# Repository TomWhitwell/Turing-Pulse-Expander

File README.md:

# Turing-Pulse-Expander
Rev 2 Turing Pulse Expander 

This is a slightly updated version of the Turing Machine Pulse Expander, with more outputs. It uses SMD components, but is still a very easy build. 

BOM: 

- 1 x 4081 Quad AND Gate, SO14 package 
- 11 x 3mm LEDs 
- 11 x 1k resistors, 1206 package 
- 11 x 2k resistors, 1206 package (These are the LED protection resistors, if you're using high intensity LEDs they should be a different value)
- 11 x [Thonkiconn](https://www.thonk.co.uk/shop/thonkiconn-3-5mm-jack-sockets-x50/) sockets
- 1 x 16 Pin Header 2x8 (for example 649-67997-216HLF from Mouser)
- 1 x Ribbon cable

There is no panel yet in this repository.

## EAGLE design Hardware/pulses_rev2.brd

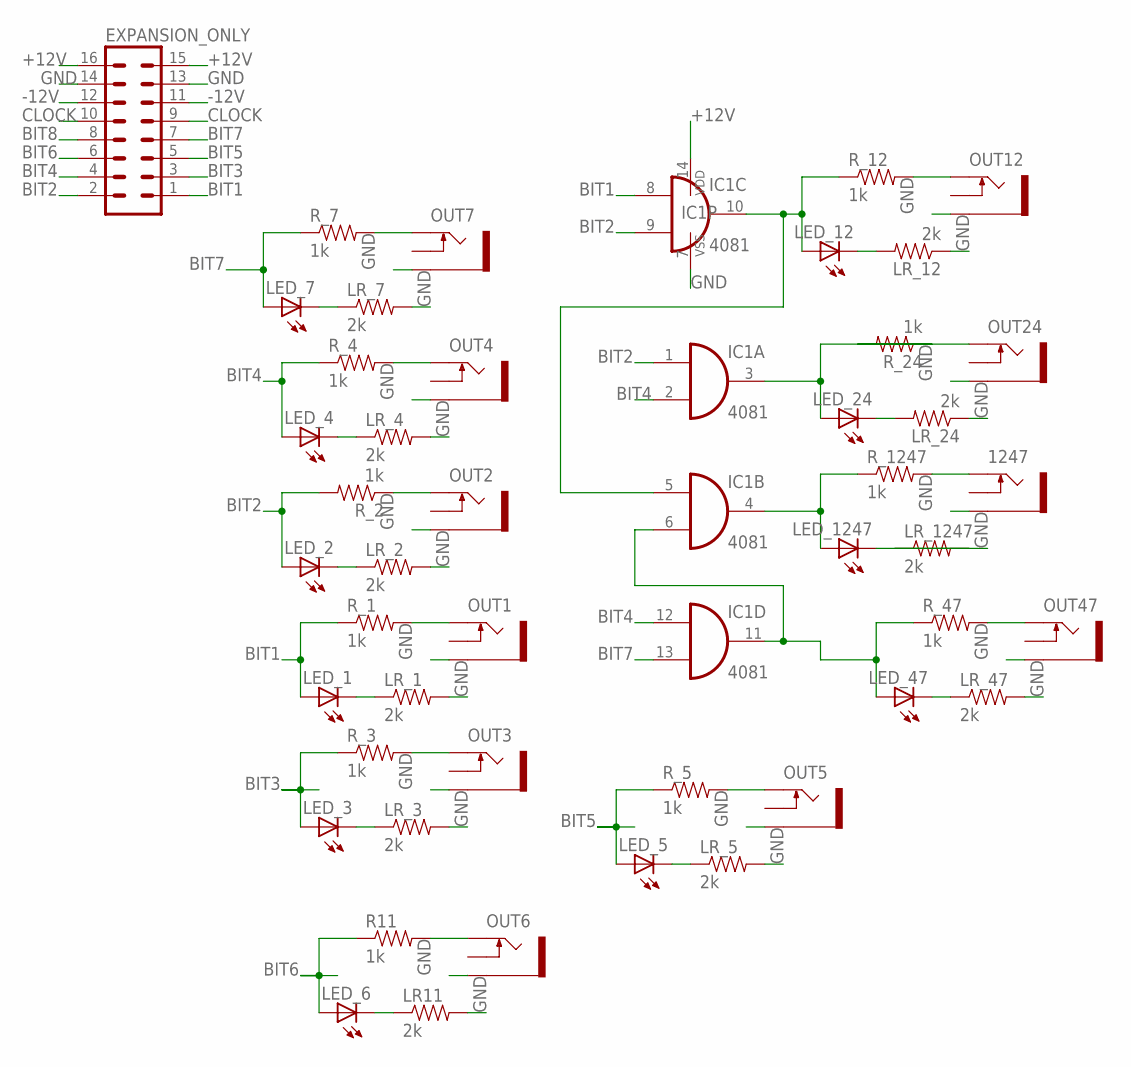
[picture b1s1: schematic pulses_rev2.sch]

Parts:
1247: THONKICONNNEW; WQP-PJ301M-12_JACK
EXPANSION_ONLY: MA08-2
IC1: 4081; SO14
LED_1, LED_2, LED_3, LED_4, LED_5, LED_6, LED_7, LED_12, LED_24, LED_47, LED_1247: LED3MM
LR11: 2k; 1206
LR_1, LR_2, LR_3, LR_4, LR_5, LR_7, LR_12, LR_24, LR_47, LR_1247: 2k; 1206
OUT1, OUT2, OUT3, OUT4, OUT5, OUT6, OUT7, OUT12, OUT24, OUT47: THONKICONNNEW; WQP-PJ301M-12_JACK
R11: 1k; 1206
R_1, R_2, R_3, R_4, R_5, R_7, R_12, R_24, R_47, R_1247: 1k; 1206

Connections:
+12V: EXPANSION_ONLY.15, EXPANSION_ONLY.16, IC1.14 (VDD)
-12V: EXPANSION_ONLY.11, EXPANSION_ONLY.12
BIT1: EXPANSION_ONLY.1, IC1.8 (I0), LED_1.A, R_1.1
BIT2: EXPANSION_ONLY.2, IC1.1 (I0), IC1.9 (I1), LED_2.A, R_2.2
BIT3: EXPANSION_ONLY.3, LED_3.A, R_3.1
BIT4: EXPANSION_ONLY.4, IC1.2 (I1), IC1.12 (I0), LED_4.A, R_4.1
BIT5: EXPANSION_ONLY.5, LED_5.A, R_5.1
BIT6: EXPANSION_ONLY.6, LED_6.A, R11.1
BIT7: EXPANSION_ONLY.7, IC1.13 (I1), LED_7.A, R_7.1
BIT8: EXPANSION_ONLY.8
BIT9: IC1.5 (I0), IC1.10 (O), LED_12.A, R_12.1
BIT10: IC1.3 (O), LED_24.A, R_24.1
BIT11: IC1.4 (O), LED_1247.A, R_1247.1
BIT12: IC1.6 (I1), IC1.11 (O), LED_47.A, R_47.1
CLOCK: EXPANSION_ONLY.9, EXPANSION_ONLY.10
GND: 1247.P$3_SLEEVE (SLEEVE), EXPANSION_ONLY.13, EXPANSION_ONLY.14, IC1.7 (VSS), LR11.2, LR_1.2, LR_2.2, LR_3.2, LR_4.2, LR_5.2, LR_7.2, LR_12.1, LR_24.1, LR_47.2, LR_1247.1, OUT1.P$3_SLEEVE (SLEEVE), OUT2.P$3_SLEEVE (SLEEVE), OUT3.P$3_SLEEVE (SLEEVE), OUT4.P$3_SLEEVE (SLEEVE), OUT5.P$3_SLEEVE (SLEEVE), OUT6.P$3_SLEEVE (SLEEVE), OUT7.P$3_SLEEVE (SLEEVE), OUT12.P$3_SLEEVE (SLEEVE), OUT24.P$3_SLEEVE (SLEEVE), OUT47.P$3_SLEEVE (SLEEVE)
unnamed: OUT1.P$1_TIP (TIP), R_1.2
unnamed: LED_1.K (C), LR_1.1
unnamed: OUT12.P$1_TIP (TIP), R_12.2
unnamed: OUT2.P$1_TIP (TIP), R_2.1
unnamed: LED_2.K (C), LR_2.1
unnamed: LED_12.K (C), LR_12.2
unnamed: OUT4.P$1_TIP (TIP), R_4.2
unnamed: LED_4.K (C), LR_4.1
unnamed: OUT24.P$1_TIP (TIP), R_24.2
unnamed: OUT7.P$1_TIP (TIP), R_7.2
unnamed: LED_7.K (C), LR_7.1
unnamed: LED_24.K (C), LR_24.2
unnamed: 1247.P$1_TIP (TIP), R_1247.2
unnamed: LED_1247.K (C), LR_1247.2
unnamed: OUT3.P$1_TIP (TIP), R_3.2
unnamed: OUT47.P$1_TIP (TIP), R_47.2
unnamed: LED_47.K (C), LR_47.1
unnamed: LED_3.K (C), LR_3.1
unnamed: OUT5.P$1_TIP (TIP), R_5.2
unnamed: LED_5.K (C), LR_5.1
unnamed: OUT6.P$1_TIP (TIP), R11.2
unnamed: LED_6.K (C), LR11.1

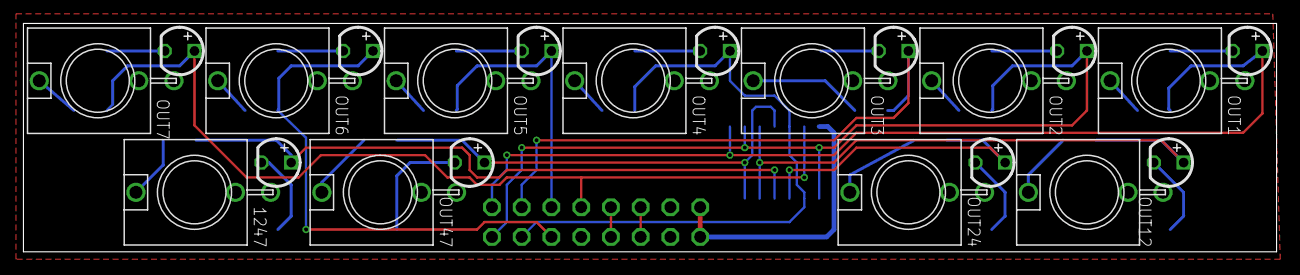
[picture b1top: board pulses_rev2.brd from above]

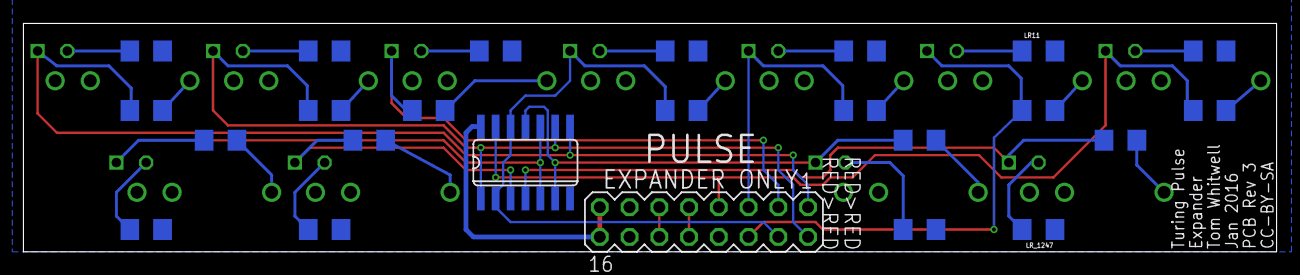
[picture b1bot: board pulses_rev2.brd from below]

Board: 4 copper layers, 107.0 x 19.5 mm, 46 parts (24 on the bottom side), 37 nets.

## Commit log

2016-01-24 Initial upload, design complete for first prototype
2016-01-25 Non functional schematic tweaks
2016-05-26 Upload panel artwork

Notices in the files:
Hardware/pulses_rev2.brd:
CC-BY-SA
parts and their libraries:
SparkFun-Passives: Licensing: CC v3.0 Share-Alike You are welcome to use this library for commercial purposes.
